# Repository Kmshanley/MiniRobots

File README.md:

# MiniRobots
 Firmware and PCB desgin for mini robots with UWB localization and lidar mapping

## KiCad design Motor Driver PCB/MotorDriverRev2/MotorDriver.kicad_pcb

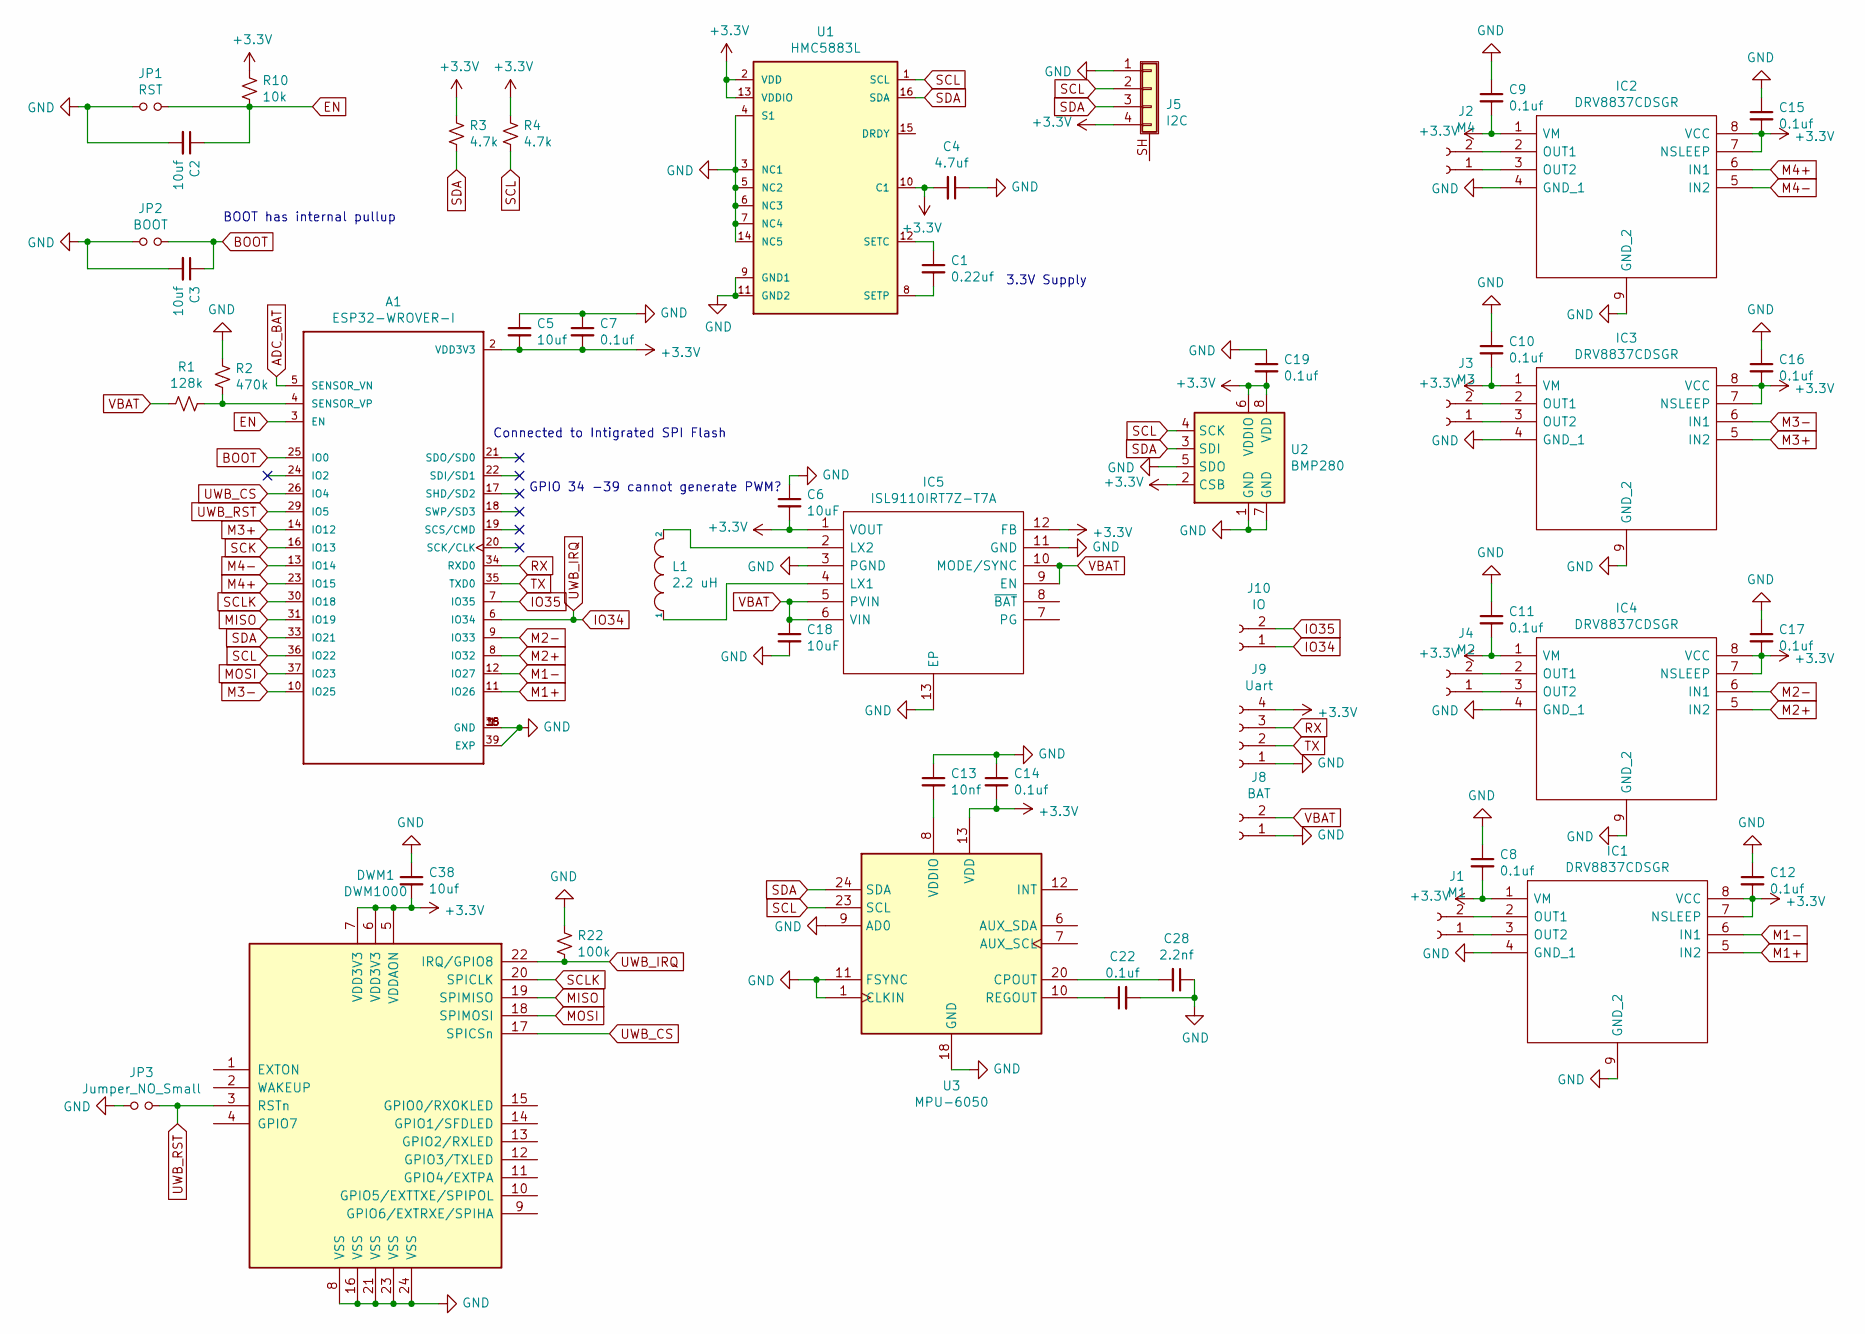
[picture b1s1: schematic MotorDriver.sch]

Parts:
A1: ESP32-WROVER-I; ESP32-WROOM-32U
C1: 0.22uf; C_0402_1005Metric
C2, C3, C5, C38: 10uf; C_0402_1005Metric
C4: 4.7uf; C_0402_1005Metric
C6, C18: 10uF; C_0402_1005Metric
C7, C8, C9, C10, C11, C12, C14, C15, C16, C17, C19, C22: 0.1uf; C_0402_1005Metric
C13: 10nf; C_0402_1005Metric
C28: 2.2nf; C_0402_1005Metric
DWM1: DWM1000
IC1, IC2, IC3, IC4: DRV8837CDSGR; SON50P200X200X80-9N; Mouser Part Number 595-DRV8837CDSGR
IC5: ISL9110IRT7Z-T7A; SON40P300X300X75-13N; Mouser Part Number 968-ISL9110IRT7Z-T7A
J1: M1; SolderWirePad_1x02_P3.81mm_Drill1mm
J2: M4; SolderWirePad_1x02_P3.81mm_Drill1mm
J3: M3; SolderWirePad_1x02_P3.81mm_Drill1mm
J4: M2; SolderWirePad_1x02_P3.81mm_Drill1mm
J5: I2C; PinHeader_1x04_P2.00mm_Vertical
J8: BAT; SolderWirePad_1x02_P3.81mm_Drill1mm
J9: Uart; PinHeader_1x04_P2.00mm_Vertical
J10: IO; PinHeader_1x02_P2.00mm_Vertical
JP1: RST; SolderJumper-2_P1.3mm_Open_Pad1.0x1.5mm
JP2: BOOT; SolderJumper-2_P1.3mm_Open_Pad1.0x1.5mm
JP3: Jumper_NO_Small; SolderJumper-2_P1.3mm_Open_Pad1.0x1.5mm
L1: 2.2 uH; LQH3NPN100MMEL
R1: 128k; R_0402_1005Metric
R2: 470k; R_0402_1005Metric
R3, R4: 4.7k; R_0402_1005Metric
R10: 10k; R_0402_1005Metric
R22: 100k; R_0402_1005Metric
U1: HMC5883L
U2: BMP280; Bosch_LGA-8_2x2.5mm_P0.65mm_ClockwisePinNumbering
U3: MPU-6050; InvenSense_QFN-24_4x4mm_P0.5mm

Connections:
+3V3: A1.2 (VDD3V3), C4.2, C5.2, C6.2, C7.2, C8.2, C9.2, C10.2, C11.2, C12.2, C14.2, C15.2, C16.2, C17.2, C19.2, C38.2, DWM1.5 (VDDAON), DWM1.6 (VDD3V3), DWM1.7 (VDD3V3), IC1.1 (VM), IC1.7 (NSLEEP), IC1.8 (VCC), IC2.1 (VM), IC2.7 (NSLEEP), IC2.8 (VCC), IC3.1 (VM), IC3.7 (NSLEEP), IC3.8 (VCC), IC4.1 (VM), IC4.7 (NSLEEP), IC4.8 (VCC), IC5.1 (VOUT), IC5.12 (FB), J5.4, J9.4, R3.1, R4.1, R10.1, U1.2 (VDD), U1.10 (C1), U1.13 (VDDIO), U2.2 (CSB), U2.6 (VDDIO), U2.8 (VDD), U3.13 (VDD)
BOOT: A1.25 (IO0), C3.1, JP2.2
EN: A1.3 (EN), C2.1, JP1.2, R10.2
GND: A1.1 (GND), A1.15 (GND), A1.38 (GND), A1.39 (EXP), C2.2, C3.2, C4.1, C5.1, C6.1, C7.1, C8.1, C9.1, C10.1, C11.1, C12.1, C13.1, C14.1, C15.1, C16.1, C17.1, C18.2, C19.1, C22.2, C28.1, C38.1, DWM1.8 (VSS), DWM1.16 (VSS), DWM1.21 (VSS), DWM1.23 (VSS), DWM1.24 (VSS), IC1.4 (GND_1), IC1.9 (GND_2), IC2.4 (GND_1), IC2.9 (GND_2), IC3.4 (GND_1), IC3.9 (GND_2), IC4.4 (GND_1), IC4.9 (GND_2), IC5.3 (PGND), IC5.11 (GND), IC5.13 (EP), J5.1, J8.1, J9.1, JP1.1, JP2.1, JP3.1, R2.1, R22.1, U1.3 (NC1), U1.4 (S1), U1.5 (NC2), U1.6 (NC3), U1.7 (NC4), U1.9 (GND1), U1.11 (GND2), U1.14 (NC5), U2.1 (GND), U2.5 (SDO), U2.7 (GND), U3.1 (CLKIN), U3.9 (AD0), U3.11 (FSYNC), U3.18 (GND)
IO34: A1.6 (IO34), DWM1.22 (IRQ/GPIO8), J10.1, R22.2
IO35: A1.7 (IO35), J10.2
M1+: A1.11 (IO26), IC1.5 (IN2)
M1-: A1.12 (IO27), IC1.6 (IN1)
M2+: A1.8 (IO32), IC4.5 (IN2)
M2-: A1.9 (IO33), IC4.6 (IN1)
M3+: A1.14 (IO12), IC3.5 (IN2)
M3-: A1.10 (IO25), IC3.6 (IN1)
M4+: A1.23 (IO15), IC2.6 (IN1)
M4-: A1.13 (IO14), IC2.5 (IN2)
MISO: A1.31 (IO19), DWM1.19 (SPIMISO)
MOSI: A1.37 (IO23), DWM1.18 (SPIMOSI)
unnamed: A1.4 (SENSOR_VP), R1.2, R2.2
unnamed: C1.1, U1.12 (SETC)
unnamed: C1.2, U1.8 (SETP)
unnamed: C13.2, U3.8 (VDDIO)
unnamed: C22.1, U3.10 (REGOUT)
unnamed: C28.2, U3.20 (CPOUT)
unnamed: IC1.2 (OUT1), J1.2
unnamed: IC1.3 (OUT2), J1.1
unnamed: IC2.2 (OUT1), J2.2
unnamed: IC2.3 (OUT2), J2.1
unnamed: IC3.2 (OUT1), J3.2
unnamed: IC3.3 (OUT2), J3.1
unnamed: IC4.2 (OUT1), J4.2
unnamed: IC4.3 (OUT2), J4.1
unnamed: IC5.2 (LX2), L1.2
unnamed: IC5.4 (LX1), L1.1
RX: A1.34 (RXD0), J9.3
SCL: A1.36 (IO22), J5.2, R4.2, U1.1 (SCL), U2.4 (SCK), U3.23 (SCL)
SCLK: A1.30 (IO18), DWM1.20 (SPICLK)
SDA: A1.33 (IO21), J5.3, R3.2, U1.16 (SDA), U2.3 (SDI), U3.24 (SDA)
TX: A1.35 (TXD0), J9.2
UWB_CS: A1.26 (IO4), DWM1.17 (SPICSn)
UWB_RST: A1.29 (IO5), DWM1.3 (RSTn), JP3.2
VBAT: C18.1, IC5.5 (PVIN), IC5.6 (VIN), IC5.9 (EN), IC5.10 (MODE/SYNC), J8.2, R1.1

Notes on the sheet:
BOOT has internal pullup
3.3V Supply
Connected to Intigrated SPI Flash
GPIO 34 -39 cannot generate PWM?

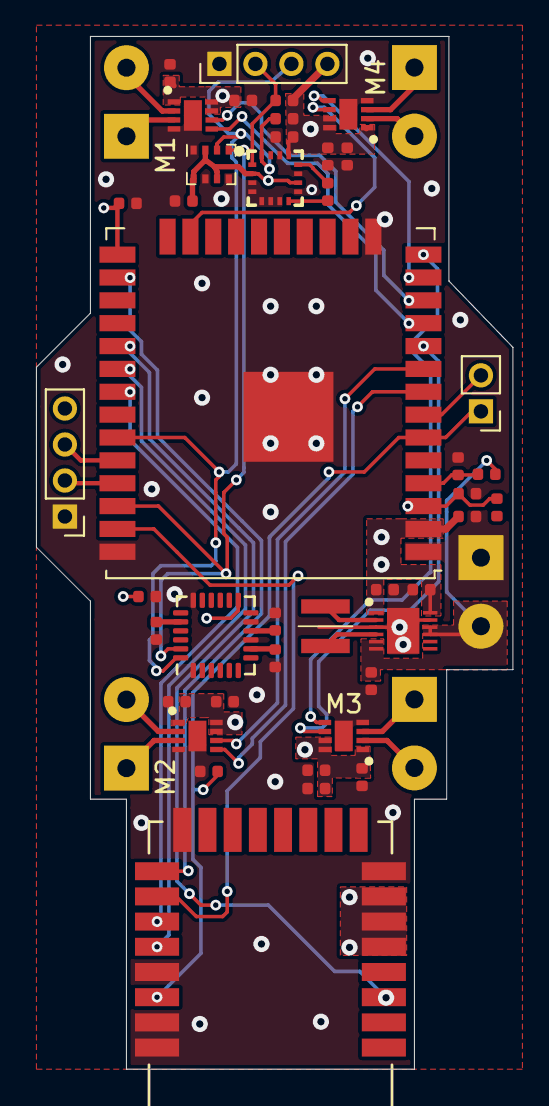
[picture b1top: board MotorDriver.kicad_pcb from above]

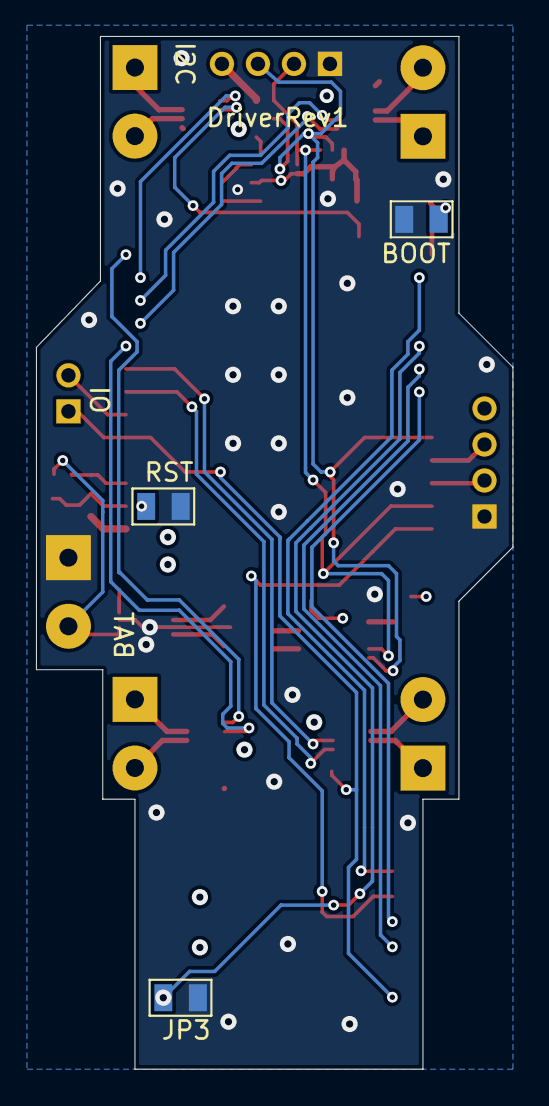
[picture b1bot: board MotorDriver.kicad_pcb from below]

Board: 4 copper layers, 26.5 x 57.4 mm, 50 parts (3 on the bottom side), 40 nets.

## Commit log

2021-10-03 Added dw3000 lib
2021-11-30 MotorDriverRev2
    New PCB design. Correct numerous errors.
